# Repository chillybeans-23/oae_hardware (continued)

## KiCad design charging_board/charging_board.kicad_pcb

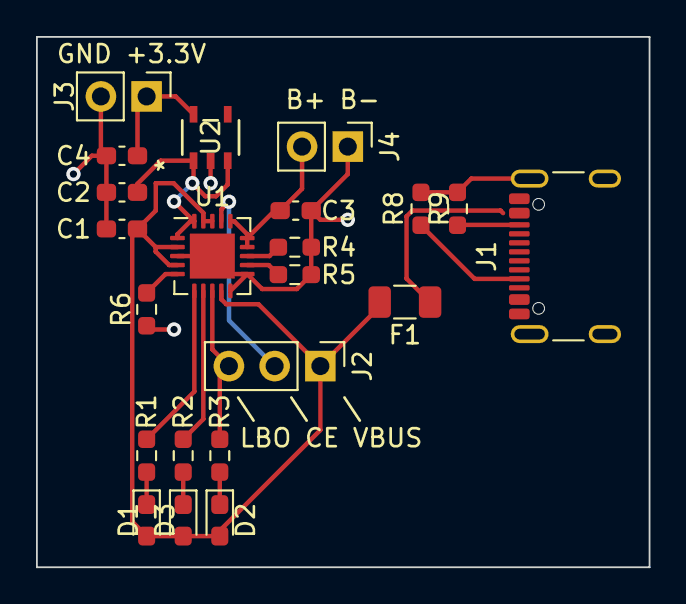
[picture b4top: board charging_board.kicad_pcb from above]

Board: 2 copper layers, 34.0 x 29.5 mm, 22 parts (0 on the bottom side), 18 nets.

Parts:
C1: 10uF; C_0603_1608Metric_Pad1.08x0.95mm_HandSolder
C2, C3, C4: 4.7uF; C_0603_1608Metric_Pad1.08x0.95mm_HandSolder
D1, D2, D3: LED; LED_0603_1608Metric_Pad1.05x0.95mm_HandSolder
F1: 1A; Fuse_1206_3216Metric
J1: USB4105-GF-A; USB_C_Receptacle_GCT_USB4105-xx-A_16P_TopMnt_Horizontal
J2: Jumper; PinHeader_1x03_P2.54mm_Vertical
J3: Conn_01x02_Pin; PinHeader_1x02_P2.54mm_Vertical
J4: Battery_connector; PinHeader_1x02_P2.54mm_Vertical
R1, R2, R3: 470; R_0603_1608Metric_Pad0.98x0.95mm_HandSolder
R4: 2k; R_0603_1608Metric_Pad0.98x0.95mm_HandSolder
R5: 8k; R_0603_1608Metric_Pad0.98x0.95mm_HandSolder
R6: 10k; R_0603_1608Metric_Pad0.98x0.95mm_HandSolder
R8, R9: 5.1K; R_0603_1608Metric_Pad0.98x0.95mm_HandSolder
U1: MCP73871-1CC; QFN-20-1EP_4x4mm_P0.5mm_EP2.5x2.5mm
U2: XC6210B332MR-G; SOT-25_TOR

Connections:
/CE: J2.2, U1.17 (CE)
/Load: C4.1, J3.1, U2.5 (VOUT)
/USB: F1.1, J1.B4 (VBUS)
/VBUS: C1.1, D1.2 (A), D2.2 (A), D3.2 (A), F1.2, J2.1, U1.2 (VPCC), U1.4 (PROG2), U1.9 (~TE), U1.18 (IN), U1.19 (IN)
/~LBO: J2.3, R3.1, U1.8 (STAT1/~LBO), U2.3 (CE)
GND: C1.2, C2.2, C3.2, C4.2, J3.2, J4.1, R4.2, R5.1, R6.1, R8.2, R9.1, U1.3 (SEL), U1.10 (V_{SS}), U1.11 (V_{SS}), U1.21 (V_{SS}), U2.2 (VSS)
unnamed: D1.1 (K), R1.2
unnamed: D2.1 (K), R3.2
unnamed: D3.1 (K), R2.2
unnamed: J1.A5 (CC1), R9.2
unnamed: J1.B5 (CC2), R8.1
unnamed: C3.1, J4.2, U1.14 (V_{BAT}), U1.15 (V_{BAT}), U1.16 (V_{BAT_SENSE})
unnamed: R4.1, U1.13 (PROG1)
unnamed: R5.2, U1.12 (PROG3)
unnamed: R2.1, U1.7 (STAT2)
unnamed: R6.2, U1.5 (THERM)
unnamed: R1.1, U1.6 (~PG)
unnamed: C2.1, U1.1 (OUT), U1.20 (OUT), U2.1 (VIN)

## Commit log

2022-10-19 initialize kicad project
2022-10-27 start schematic design
2022-11-15 add microcontroller schematics
2022-11-17 fix grid, change to use a separate gnd plane for analog
2022-11-29 first pass layout
2022-11-29 update pdf
2022-11-29 udpate ground planes to remove as many big cutouts
2022-11-29 add analog and digital labels to the user plane
2023-03-27 update pcb to what was shipped
2023-05-05 add external 21 bit adc
2023-07-07 Create second revision of OAE schematic
    * Adjusted signal chain amplification issue in schematic
    * Removed schematic short; Added LTSpice schmatic for circuit validation
    * Rearranged buffer/amplifier components on PCB (See comment)
    * Changed LME49723 to MCP6001 RtR
    * Moved voltage divider to non-inverting input
    * Add ADC communication lines
2023-07-10 Organized layout chunks
2023-07-12 Iterated first layout design
2023-07-13 Compressed trace parallelization
2023-07-13 Reduced board size
2023-07-13 Added copper fill zone and silkscreen labels
2023-07-17 Add meanders to I2S & condense board parts
2023-07-17 Change silkscreen
2023-07-18 Fix footprint
2023-07-18 Place power fill
2023-07-18 Reduce signal vias
2023-07-18 Fix capacitor footprints
2023-07-19 Add names to silkscreen
2023-07-19 Add teardrop vias and 3d models
2023-07-19 Change 1V6 line routing
2023-07-19 Beautify silk screen
2023-07-19 Move usb to board edge
2023-07-19 Changes made during presentation
2023-07-21 Fix trace related issues
2023-07-24 Fix resistor symbol
2023-07-24 Fix symbols in schematic
2023-07-24 Assign reference numbers
    This commit might need to be reset and undone.
    As of right now, everything works with the PCB.
    This needs to be checked on other computers.
2023-07-24 Fillet board edge and remake teardrops
2023-07-24 Change DRC requirements & route unconnected trace
2023-07-25 PCB Redesign (#2)
2023-07-26 Restore schematic and update pcb to match
2023-07-26 Update board to what was shipped
2023-07-26 Make value changes for most components
2023-07-26 Fixed schematic value for overlapping components
2023-07-26 Commit changes to BOM
2023-07-26 Update MSC AC coupling capacitor
2023-07-27 Regenerate teardrops and set speaker capacitors
2023-07-28 Fix silkscreen issues
2023-07-28 Fix Values while Matching References (#4)
    * Update board to what was shipped
    * Make value changes for most components
    * Fixed schematic value for overlapping components
    * Commit changes to BOM
    * Update MSC AC coupling capacitor
    * Regenerate teardrops and set speaker capacitors
2024-03-07 Add charging circuitry and footprints/symbols
2024-05-05 add charging stuff
2024-06-21 Add mechanical and electrical probe tip design
2024-06-24 Route PCB and arrange silkscreen layer
2024-06-24 Create gerber and drill files
2024-06-25 Save bad clearance version
    Clearances do not match JLCPCB's standards for fab. Saving and starting layout again
2024-06-28 Reroute PCB, change footprints, add ground fill plane
2024-07-01 Fix acute angled traces on pads
2024-07-01 Make gerber file
2024-07-02 Commit stash
2024-07-08 Make fitment changes to CAD
2024-07-09 Organize files and fix benji's probe nozzle design
2024-07-10 add new mcu in stm32l4 series for more ram
2024-07-12 Add HDMI connector and BMS header pin connector
2024-07-15 No change
2024-07-17 edit bms port
2024-07-17 update pcb layout with new mcu
2024-07-18 Arrange silkscreen elements
2024-07-19 update changes to hdmi cable, add new components in layout
2024-07-19 fix 3d models, finish layout 1st draft
2024-07-22 fix gnd via, update back silkscreen
2024-07-23 add bom and footprint positions
2024-07-23 Update schematic design
2024-07-26 Update schematic and lib files
2024-10-27 add arduino-based UI prototype code
    prototype used in midwife interview 10/18/2024
2024-11-22 Set up new environment for V2_PCB
2024-11-30 Remake schematic
2024-12-04 Update layout
2024-12-13 Update PCB outline to use Benji's probe chassis (allows for larger probe PCB)
2024-12-13 Reroute and regenerate gerber files
2024-12-13 Generate step file of populated board
2025-02-09 update to kicad 8
2025-02-09 revert "update to kicad 8"
    this reverts commit df91ba69a053605010989058b68ccee6b0fb54dd.
2025-02-10 Add OAE CliffBar (#5)
    * add new mcu in stm32l4 series for more ram
    * Add HDMI connector and BMS header pin connector
    * edit bms port
    * update pcb layout with new mcu
    * update changes to hdmi cable, add new components in layout
    * fix 3d models, finish layout 1st draft
2025-02-26 Add new main+BMS layout with right dimension
    draft 1 - before team discussion
2025-03-18 Added readme
